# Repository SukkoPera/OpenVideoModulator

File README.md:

# OpenVideoModulator
OpenVideoModulator is an Open Hardware adapter that converts an RGB video signal to Composite and S-Video.

## Summary
OpenVideoModulator is an Open Hardware implementation of [a small circuit found on the Amstrad CPC Wiki](http://www.cpcwiki.eu/index.php/RGB_SVideo) that is able to produce a composite video signal from separate red, green and blue color component signals (plus sync). Since it uses the AD724 encoder, it is also able to produce an S-Video (Y/C) signal and it supports both the PAL and NTSC standards.

It has a compact form factor, a low component count and it only requires a +5V power supply. This makes it useful with old computers that do not have a native composite or S-Video output, like the Amstrad CPC or the Commodore Amiga 500 (which actually has a composite output but it's only black & white). It also tries to maintain the smallest possible form factor, which might allow for an internal installation.

## Assembly and Usage
First of all you need to choose whether you want PAL or NTSC output. The board is preconfigured for PAL, if you need NTSC you will need to cut the link between pads 1-2 on the top of the board and solder 2-3 together. The crystal frequency also depends on your choice: use 4.433619 MHz for PAL or 3.579545 MHz for NTSC.

Solder the AD724 chip first, then all surface-mount components. Finally complete the board with the through-hole connectors and crystal.

One of C6 and C7 should be enough. I use a 100uF on C6 but that is probably overkill. Play with them if your output video signal is unstable.

The Composite/S-Video connector can be found from many Chinese sellers under the name *AV-MDC-401*. I chose this one as it was perfect for my needs, but the board should be easy to adapt to different connectors.

Usage should be straightforward: just provide power (make sure to match the polarity!) and video signals to the board, then get your output from the other side. Note that the *sync* input requires a *composite sync* signal.

## License
The OpenVideoModulator documentation, including the design itself, is copyright &copy; SukkoPera 2019-2020.

OpenVideoModulator is Open Hardware licensed under the [CERN OHL v. 1.2](http://ohwr.org/cernohl).

You may redistribute and modify this documentation under the terms of the CERN OHL v.1.2. This documentation is distributed *as is* and WITHOUT ANY EXPRESS OR IMPLIED WARRANTIES whatsoever with respect to its functionality, operability or use, including, without limitation, any implied warranties OF MERCHANTABILITY, SATISFACTORY QUALITY, FITNESS FOR A PARTICULAR PURPOSE or infringement. We expressly disclaim any liability whatsoever for any direct, indirect, consequential, incidental or special damages, including, without limitation, lost revenues, lost profits, losses resulting from business interruption or loss of data, regardless of the form of action or legal theory under which the liability may be asserted, even if advised of the possibility or likelihood of such damages.

A copy of the full license is included in file [LICENSE.pdf](LICENSE.pdf), please refer to it for applicable conditions. In order to properly deal with its terms, please see file [LICENSE_HOWTO.pdf](LICENSE_HOWTO.pdf).

The contact points for information about manufactured Products (see section 4.2) are listed in file [PRODUCT.md](PRODUCT.md).

Any modifications made by Licensees (see section 3.4.b) shall be recorded in file [CHANGES.md](CHANGES.md).

The Documentation Location of the original project is https://github.com/SukkoPera/OpenVideoModulator/.

## Support the Project
Since the project is open you are free to get the PCBs made by your preferred manufacturer, however in case you want to support the development, you can order them from PCBWay through this link:

You get my gratitude and cheap, professionally-made and good quality PCBs, I get some credit that will help with this and [other projects](https://www.pcbway.com/project/member/shareproject/?bmbid=41100). You won't even have to worry about the various PCB options, it's all pre-configured for you!

Also, if you still have to register to that site, [you can use this link](https://www.pcbway.com/setinvite.aspx?inviteid=41100) to get some bonus initial credit (and yield me some more).

Again, if you want to use another manufacturer, feel free to, don't feel obligated :). But then you can buy me a coffee if you want:

## Thanks
- CPC Wiki for the original circuit.

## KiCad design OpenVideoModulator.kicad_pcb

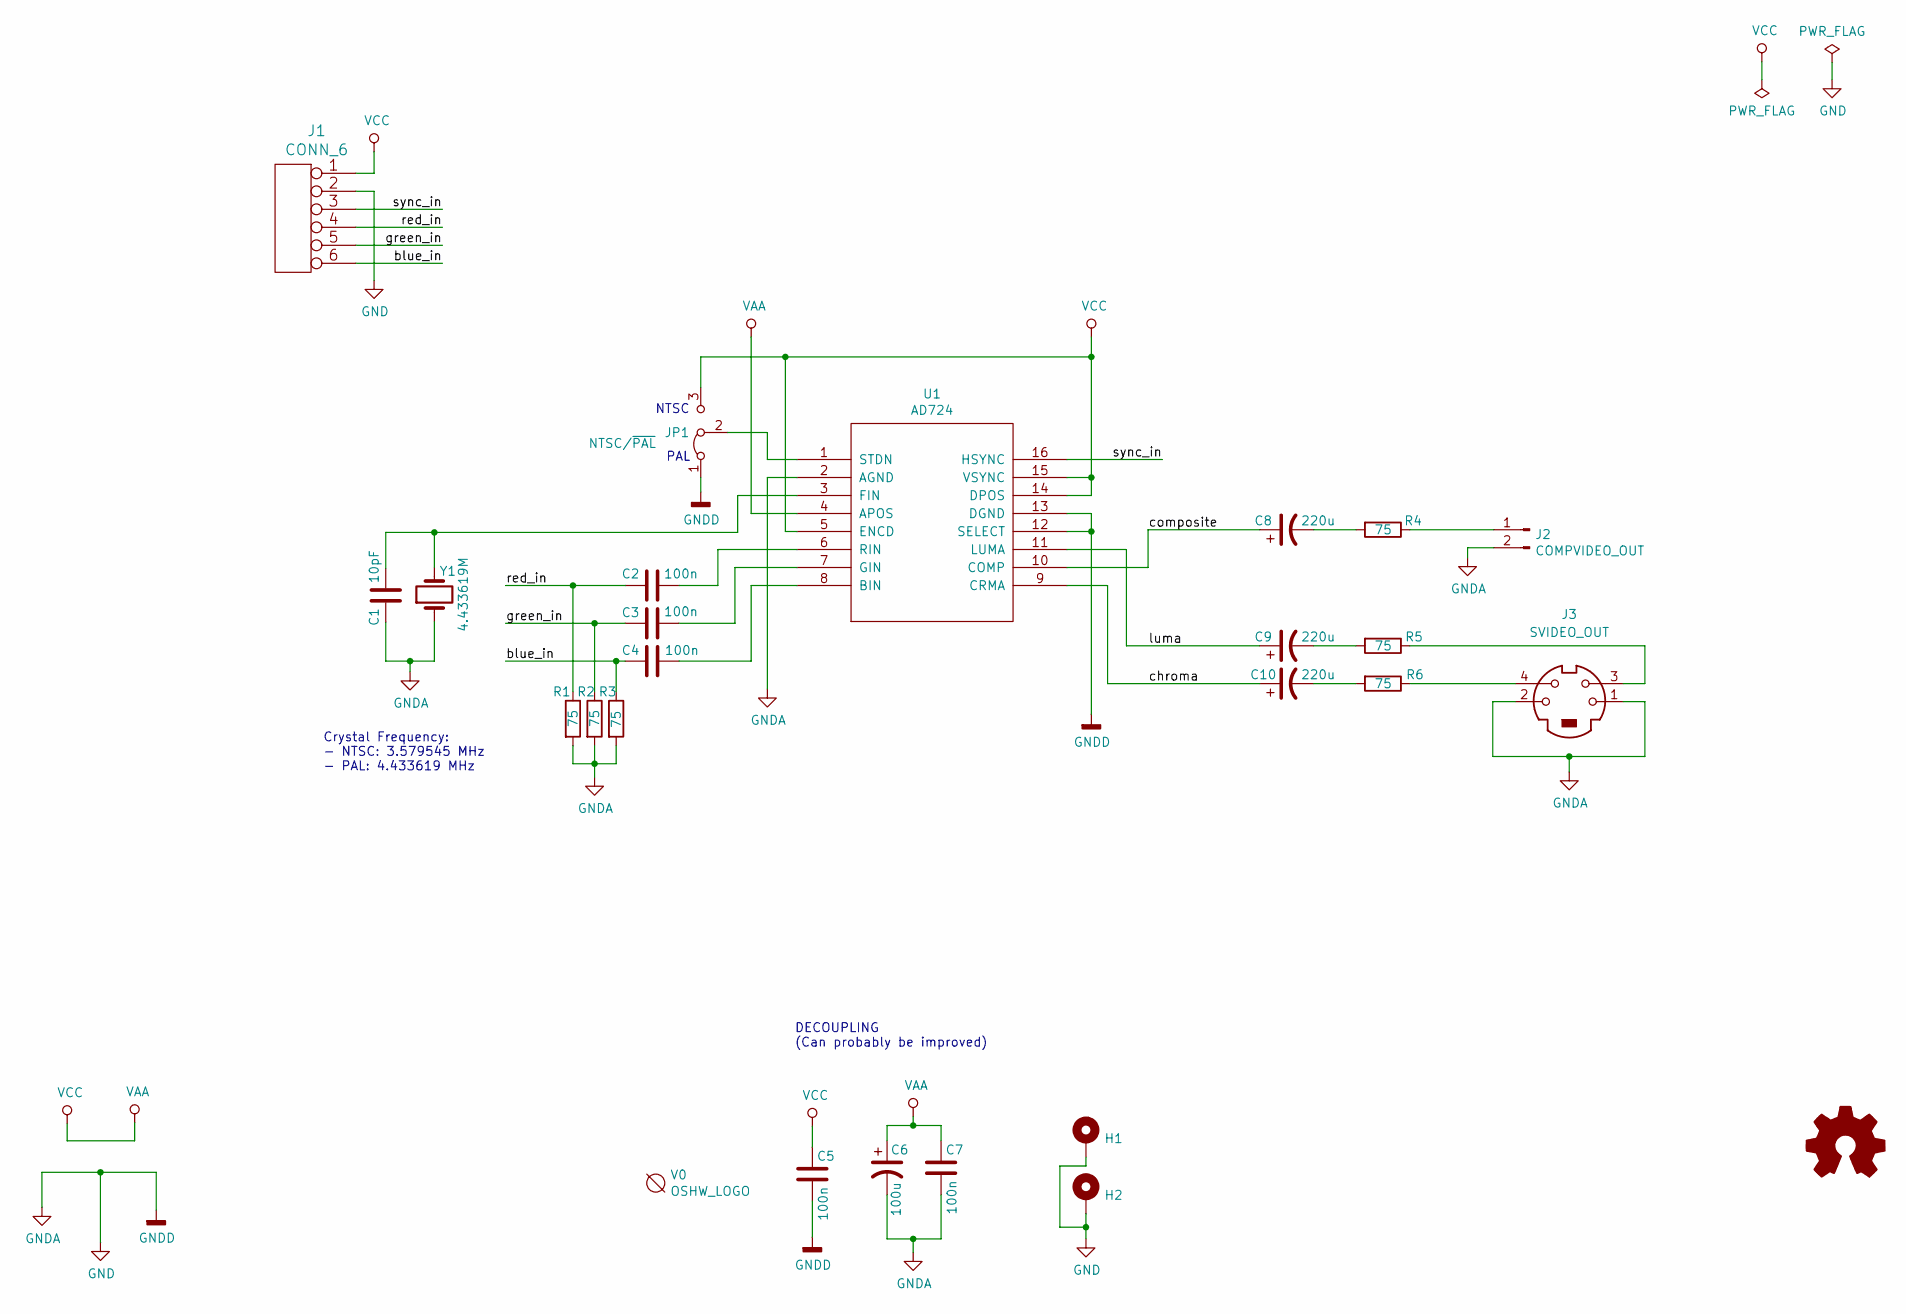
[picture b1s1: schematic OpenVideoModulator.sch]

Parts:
C1: 10pF; C_0805_2012Metric_Pad1.15x1.40mm_HandSolder
C2, C3, C4, C5: 100n; C_0805_2012Metric_Pad1.15x1.40mm_HandSolder
C6: 100u; CP_Elec_6.3x5.8
C7: 100n; C_1206_3216Metric_Pad1.42x1.75mm_HandSolder
C8, C9, C10: 220u; CP_Radial_D6.3mm_P2.50mm
H1, H2: MountingHole_Pad; MountingHole_3.2mm_M3_Pad
J1: CONN_6; PinHeader_1x06_P2.54mm_Vertical
J2: COMPVIDEO_OUT; Pin_Header_Straight_1x02-ModSilkS
J3: SVIDEO_OUT; MiniDIN4
JP1: NTSC/~PAL; SolderJumper-3_P1.3mm_Bridged12_RoundedPad1.0x1.5mm
R1, R2, R3, R4, R5, R6: 75; R_0805_2012Metric_Pad1.15x1.40mm_HandSolder
U1: AD724; SOIC-16W_7.5x10.3mm_P1.27mm
V0: OSHW_LOGO; oshw_logo
Y1: 4.433619M; Crystal_HC49-4H_Vertical

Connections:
/blue_in: C4.2, J1.6, R3.1
/chroma: C10.1, U1.9 (CRMA)
/composite: C8.1, U1.10 (COMP)
/green_in: C3.2, J1.5, R2.1
/luma: C9.1, U1.11 (LUMA)
/red_in: C2.2, J1.4, R1.1
/sync_in: J1.3, U1.16 (HSYNC)
GND: C1.2, C5.1, C6.2, C7.1, H1.1, H2.1, J1.2, J2.2, J3.0, J3.1, J3.2, JP1.1 (A), R1.2, R2.2, R3.2, U1.2 (AGND), U1.12 (SELECT), U1.13 (DGND), Y1.1
unnamed: C1.1, U1.3 (FIN), Y1.2
unnamed: C2.1, U1.6 (RIN)
unnamed: C3.1, U1.7 (GIN)
unnamed: C4.1, U1.8 (BIN)
unnamed: C8.2, R4.2
unnamed: C9.2, R5.2
unnamed: C10.2, R6.2
unnamed: J2.1, R4.1
unnamed: J3.3, R5.1
unnamed: J3.4, R6.1
unnamed: JP1.2 (C), U1.1 (STDN)
VAA: C5.2, C6.1, C7.2, J1.1, JP1.3 (B), U1.4 (APOS), U1.5 (ENCD), U1.14 (DPOS), U1.15 (VSYNC)

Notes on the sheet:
PAL
NTSC
Crystal Frequency: - NTSC: 3.579545 MHz - PAL: 4.433619 MHz
DECOUPLING (Can probably be improved)

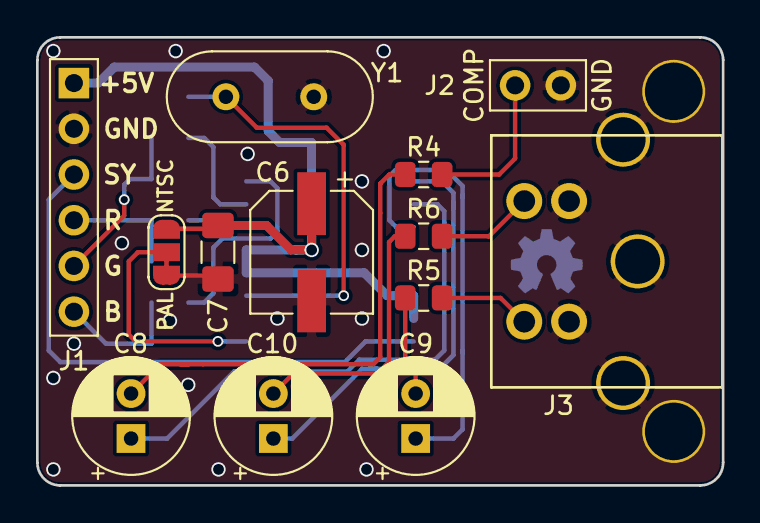
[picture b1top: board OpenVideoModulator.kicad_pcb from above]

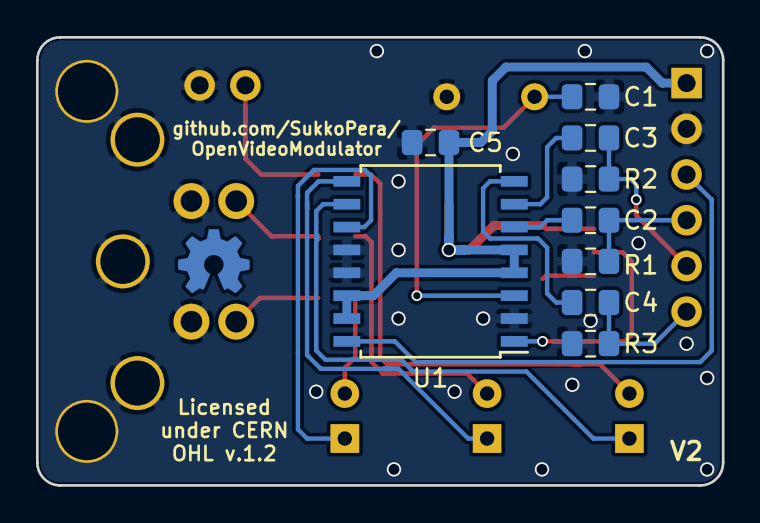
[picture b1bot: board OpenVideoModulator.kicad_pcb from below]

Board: 2 copper layers, 38.1 x 24.9 mm, 25 parts (10 on the bottom side), 20 nets.

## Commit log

2019-03-20 Almost there...
2019-03-20 Add missing footprint
2019-03-21 Minor fixes
2019-03-21 More fixes
2019-03-21 Add license
2019-03-21 Use 6.3mm electrolytics, as 220uF seem to be more common this size At least >= 16V models, which are recommended
2019-03-21 Stitch grounds
2019-03-21 Ground S-Video connector shielding... AND READY FOR V1!
2020-03-29 Final touches for release
2020-03-29 Add renders
2020-03-29 Add AV-MDC-401 drawing
2020-04-29 Fix PAL crystal frequency (Closes #1)
2020-04-29 V2 with RCA connector for composite video only
2020-04-29 Rename J2
2020-04-29 Connect MiniDIN shield
2020-04-29 Done
2020-04-29 V2 with S-Video connector only
2020-04-29 Fix dimensions
2026-02-13 Update donation link and remove help section
    Updated the coffee donation link and removed the help section.

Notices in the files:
OpenVideoModulator.kicad_pcb:
Licensed under CERN OHL v.1.2
